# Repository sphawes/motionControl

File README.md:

This is the repository for the motion control rig used in this video series:

https://www.youtube.com/watch?v=dO9BP5LPpvc&list=PLIeJXmcg1baKayRlP0rPVfIoyxI9K9v8s

A script in Blender exports Gcode that standard GRBL will interpret, and move the machine the same as the animation in Blender

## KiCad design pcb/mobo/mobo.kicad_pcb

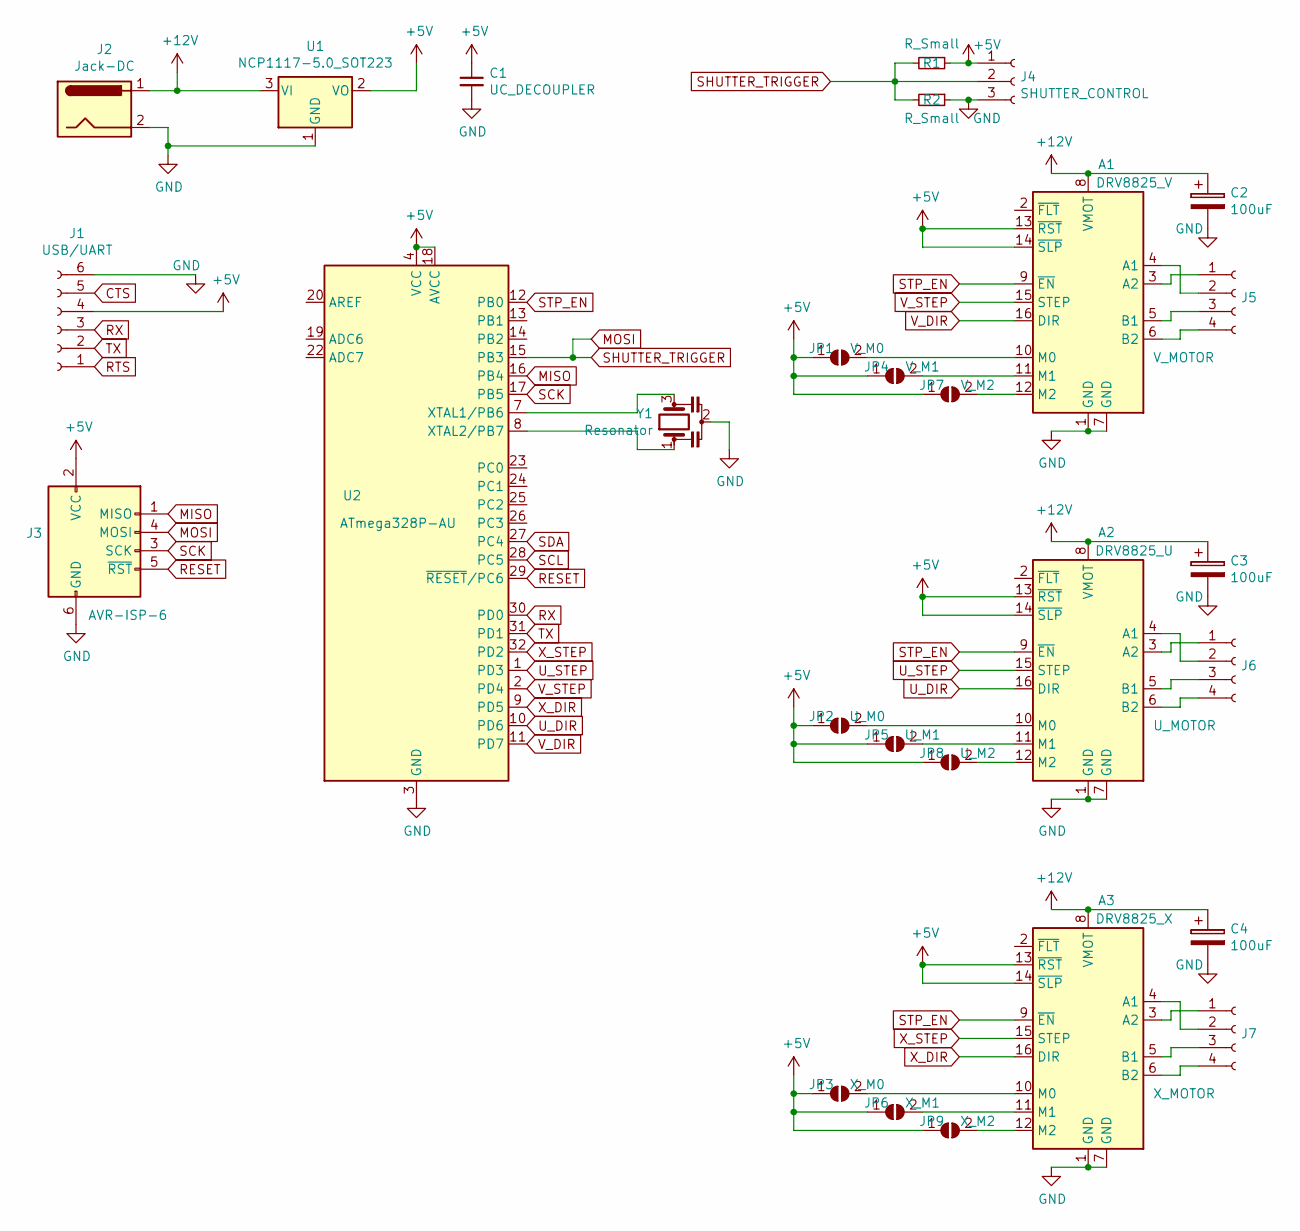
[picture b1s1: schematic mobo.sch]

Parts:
A1: DRV8825_V; Pololu_Breakout-16_15.2x20.3mm
A2: DRV8825_U; Pololu_Breakout-16_15.2x20.3mm
A3: DRV8825_X; Pololu_Breakout-16_15.2x20.3mm
C1: UC_DECOUPLER; C_0805_2012Metric_Pad1.15x1.40mm_HandSolder
C2, C3, C4: 100uF; CP_Radial_D5.0mm_P2.50mm
J1: USB/UART; PinHeader_1x06_P2.54mm_Vertical
J2: Jack-DC; BarrelJack_Horizontal
J3: AVR-ISP-6; PinSocket_2x03_P2.54mm_Vertical
J4: SHUTTER_CONTROL; PinSocket_1x03_P2.54mm_Vertical
J5: V_MOTOR; PinHeader_1x04_P2.54mm_Vertical
J6: U_MOTOR; PinHeader_1x04_P2.54mm_Vertical
J7: X_MOTOR; PinHeader_1x04_P2.54mm_Vertical
JP1: V_M0; SolderJumper-2_P1.3mm_Open_RoundedPad1.0x1.5mm
JP2: U_M0; SolderJumper-2_P1.3mm_Open_RoundedPad1.0x1.5mm
JP3: X_M0; SolderJumper-2_P1.3mm_Open_RoundedPad1.0x1.5mm
JP4: V_M1; SolderJumper-2_P1.3mm_Open_RoundedPad1.0x1.5mm
JP5: U_M1; SolderJumper-2_P1.3mm_Open_RoundedPad1.0x1.5mm
JP6: X_M1; SolderJumper-2_P1.3mm_Open_RoundedPad1.0x1.5mm
JP7: V_M2; SolderJumper-2_P1.3mm_Open_RoundedPad1.0x1.5mm
JP8: U_M2; SolderJumper-2_P1.3mm_Open_RoundedPad1.0x1.5mm
JP9: X_M2; SolderJumper-2_P1.3mm_Open_RoundedPad1.0x1.5mm
R1, R2: R_Small; R_0805_2012Metric_Pad1.15x1.40mm_HandSolder
U1: NCP1117-5.0_SOT223; SOT-223-3_TabPin2
U2: ATmega328P-AU; TQFP-32_7x7mm_P0.8mm
Y1: Resonator; Resonator_SMD_muRata_CSTxExxV-3Pin_3.0x1.1mm_HandSoldering

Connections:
+5V: A1.13 (~RST), A1.14 (~SLP), A2.13 (~RST), A2.14 (~SLP), A3.13 (~RST), A3.14 (~SLP), C1.1, J1.4, J3.2 (VCC), J4.1, JP1.1 (A), JP2.1 (A), JP3.1 (A), JP4.1 (A), JP5.1 (A), JP6.1 (A), JP7.1 (A), JP8.1 (A), JP9.1 (A), R1.1, U1.2 (VO), U2.4 (VCC), U2.6 (VCC), U2.18 (AVCC)
+12V: A1.8 (VMOT), A2.8 (VMOT), A3.8 (VMOT), C2.1, C3.1, C4.1, J2.1, U1.3 (VI)
CTS: J1.5
GND: A1.1 (GND), A1.7 (GND), A2.1 (GND), A2.7 (GND), A3.1 (GND), A3.7 (GND), C1.2, C2.2, C3.2, C4.2, J1.6, J2.2, J3.6 (GND), J4.3, R2.1, U1.1 (GND), U2.3 (GND), U2.5 (GND), U2.21 (GND), Y1.2
MISO: J3.1 (MISO), U2.16 (PB4)
MOSI: J3.4 (MOSI), J4.2, R1.2, R2.2, U2.15 (PB3)
unnamed: A1.3 (A2), J5.1
unnamed: A1.4 (A1), J5.2
unnamed: A1.5 (B1), J5.3
unnamed: A1.6 (B2), J5.4
unnamed: A1.10 (M0), JP1.2 (B)
unnamed: A1.11 (M1), JP4.2 (B)
unnamed: A1.12 (M2), JP7.2 (B)
unnamed: A2.3 (A2), J6.1
unnamed: A2.4 (A1), J6.2
unnamed: A2.5 (B1), J6.3
unnamed: A2.6 (B2), J6.4
unnamed: A2.10 (M0), JP2.2 (B)
unnamed: A2.11 (M1), JP5.2 (B)
unnamed: A2.12 (M2), JP8.2 (B)
unnamed: A3.3 (A2), J7.1
unnamed: A3.4 (A1), J7.2
unnamed: A3.5 (B1), J7.3
unnamed: A3.6 (B2), J7.4
unnamed: A3.10 (M0), JP3.2 (B)
unnamed: A3.11 (M1), JP6.2 (B)
unnamed: A3.12 (M2), JP9.2 (B)
unnamed: U2.7 (XTAL1/PB6), Y1.3
unnamed: U2.8 (XTAL2/PB7), Y1.1
RESET: J3.5 (~RST), U2.29 (~RESET~/PC6)
RTS: J1.1
RX: J1.3, U2.30 (PD0)
SCK: J3.3 (SCK), U2.17 (PB5)
SCL: U2.28 (PC5)
SDA: U2.27 (PC4)
STP_EN: A1.9 (~EN), A2.9 (~EN), A3.9 (~EN), U2.12 (PB0)
TX: J1.2, U2.31 (PD1)
U_DIR: A2.16 (DIR), U2.10 (PD6)
U_STEP: A2.15 (STEP), U2.1 (PD3)
V_DIR: A1.16 (DIR), U2.11 (PD7)
V_STEP: A1.15 (STEP), U2.2 (PD4)
X_DIR: A3.16 (DIR), U2.9 (PD5)
X_STEP: A3.15 (STEP), U2.32 (PD2)

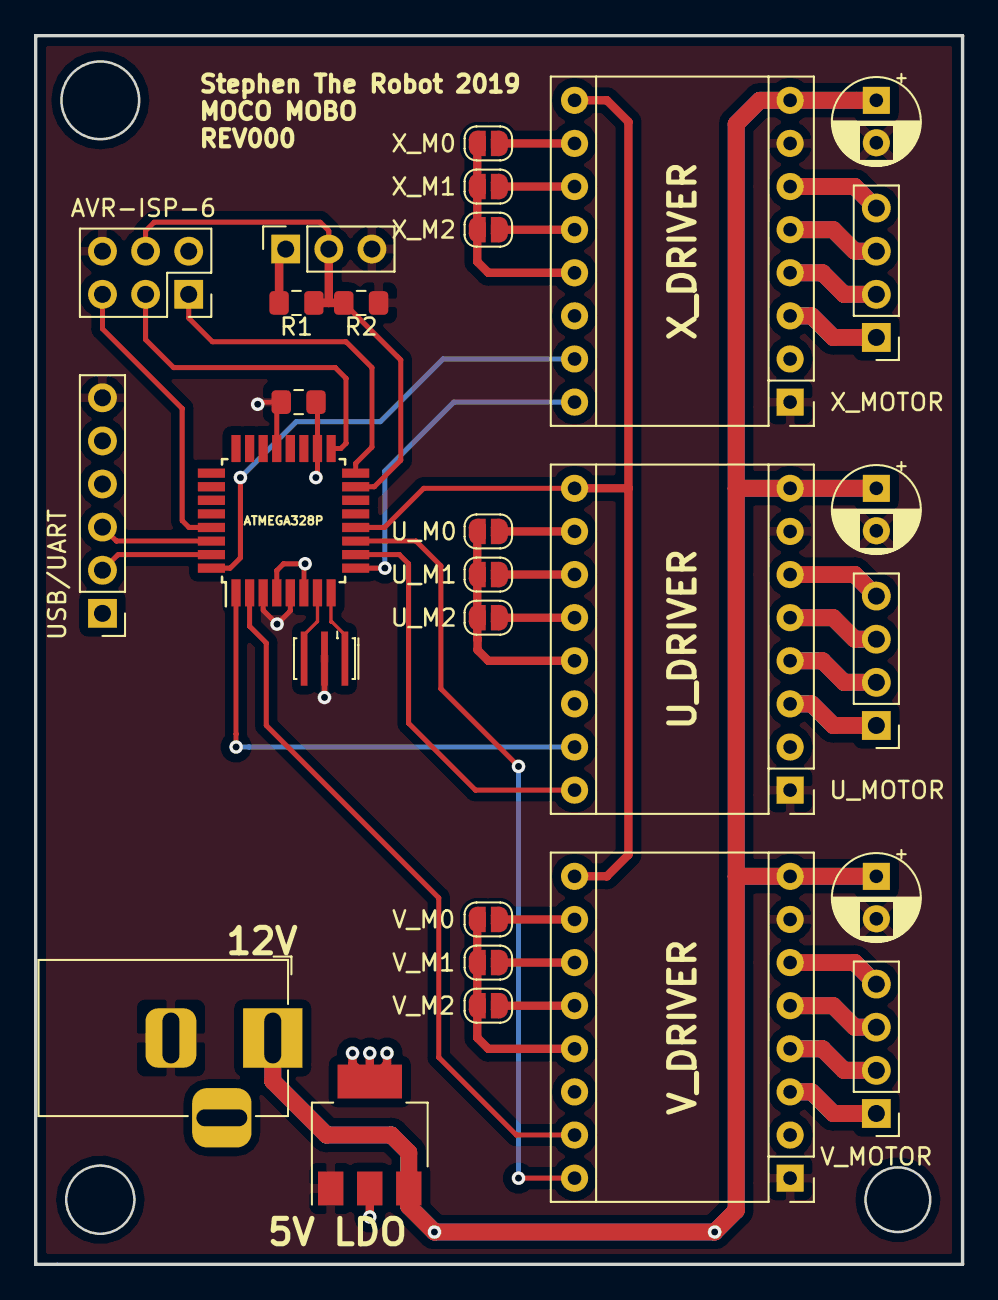
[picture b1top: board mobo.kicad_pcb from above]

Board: 4 copper layers, 54.6 x 72.4 mm, 28 parts (0 on the bottom side), 39 nets.

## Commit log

2020-05-16 updated .gitignore, added contents to readme
